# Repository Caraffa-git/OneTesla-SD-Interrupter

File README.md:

# OneTesla SD Interrupter 

re-created OneTesla SD Interrupter PCB based on files from [this page](https://onetesla.com/downloads)   

"original" version is PCB that tries to mimic the OneTesla PCB (with some small improvements), on the other hand "modified" version (for example) doesn't have useless battery holder footprints and has different layout

#### Note:
you have to install 1.1.4 version of SDFat lib for interrupter software, newer versions doesn't work

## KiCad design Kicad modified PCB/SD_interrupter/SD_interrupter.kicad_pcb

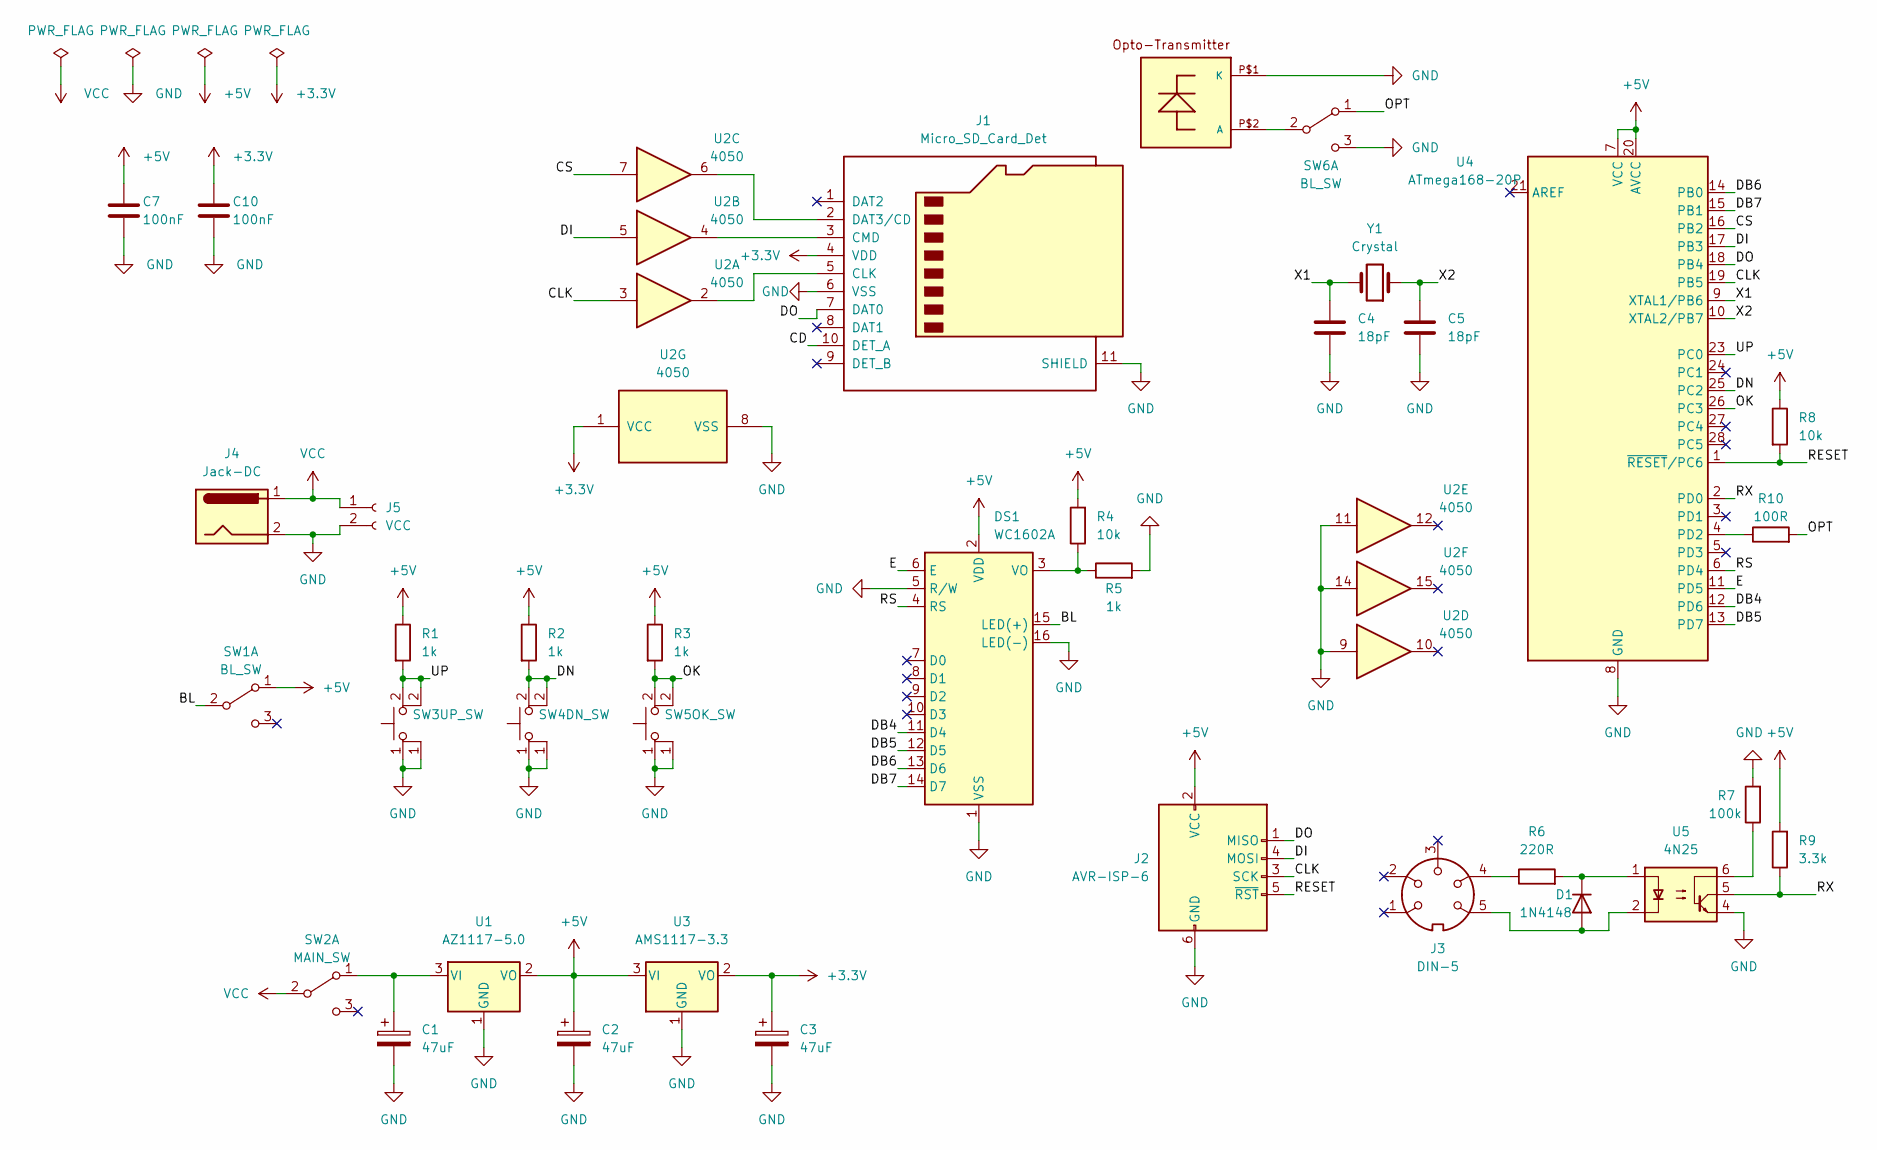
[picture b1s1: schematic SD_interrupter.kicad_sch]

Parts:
C1, C2, C3: 47uF; CP_Radial_D4.0mm_P1.50mm
C4, C5: 18pF; C_Disc_D5.1mm_W3.2mm_P5.00mm
C7, C10: 100nF; C_Disc_D5.1mm_W3.2mm_P5.00mm
D1: 1N4148; D_DO-35_SOD27_P7.62mm_Horizontal
DS1: WC1602A
J1: Micro_SD_Card_Det; microSD_HC_Hirose_DM3AT-SF-PEJM5
J2: AVR-ISP-6; PinSocket_2x03_P2.54mm_Vertical
J3: DIN-5; din-5
J4: Jack-DC; BarrelJack_Horizontal
J5: VCC; PinSocket_1x02_P2.54mm_Vertical
R1, R2, R3, R5: 1k; R_Axial_DIN0204_L3.6mm_D1.6mm_P7.62mm_Horizontal
R4, R8: 10k; R_Axial_DIN0204_L3.6mm_D1.6mm_P7.62mm_Horizontal
R6: 220R; R_Axial_DIN0204_L3.6mm_D1.6mm_P7.62mm_Horizontal
R7: 100k; R_Axial_DIN0204_L3.6mm_D1.6mm_P7.62mm_Horizontal
R9: 3.3k; R_Axial_DIN0204_L3.6mm_D1.6mm_P7.62mm_Horizontal
R10: 100R; R_Axial_DIN0204_L3.6mm_D1.6mm_P7.62mm_Horizontal
SW1, SW6: BL_SW; Switch 12x6mm
SW2: MAIN_SW; Switch 12x6mm
SW3: UP_SW; SW_PUSH_6mm_H7.3mm
SW4: DN_SW; SW_PUSH_6mm_H7.3mm
SW5: OK_SW; SW_PUSH_6mm_H7.3mm
U1: AZ1117-5.0; SOT-223-3_TabPin2
U2: 4050; DIP-16_W7.62mm
U3: AMS1117-3.3; SOT-223-3_TabPin2
U4: ATmega168-20P; DIP-28_W7.62mm
U5: 4N25; DIP-6_W7.62mm
U6: IFE91A; OPTO-TRANSMITTER
Y1: Crystal; Crystal_HC49-4H_Vertical

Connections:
+3.3V: C3.1, C10.1, J1.4 (VDD), U2.1 (VCC), U3.2 (VO)
+5V: C2.1, C7.1, DS1.2 (VDD), J2.2 (VCC), R1.1, R2.1, R3.1, R4.2, R8.1, R9.2, SW1.1 (A), U1.2 (VO), U3.3 (VI), U4.7 (VCC), U4.20 (AVCC)
/BL: DS1.15 (LED(+)), SW1.2 (B)
/CD: J1.10 (DET_A)
/CLK: J2.3 (SCK), U2.3, U4.19 (PB5)
/CS: U2.7, U4.16 (PB2)
/DB4: DS1.11 (D4), U4.12 (PD6)
/DB5: DS1.12 (D5), U4.13 (PD7)
/DB6: DS1.13 (D6), U4.14 (PB0)
/DB7: DS1.14 (D7), U4.15 (PB1)
/DI: J2.4 (MOSI), U2.5, U4.17 (PB3)
/DN: R2.2, SW4.2 (K), U4.25 (PC2)
/DO: J1.7 (DAT0), J2.1 (MISO), U4.18 (PB4)
/E: DS1.6 (E), U4.11 (PD5)
/OK: R3.2, SW5.2 (K), U4.26 (PC3)
/OPT: R10.2, SW6.1 (A)
/RESET: J2.5 (~RST), R8.2, U4.1 (~RESET/PC6)
/RS: DS1.4 (RS), U4.6 (PD4)
/RX: R9.1, U4.2 (PD0), U5.5
/UP: R1.2, SW3.2 (K), U4.23 (PC0)
/X1: C4.1, U4.9 (XTAL1/PB6), Y1.2
/X2: C5.1, U4.10 (XTAL2/PB7), Y1.1
GND: C1.2, C2.2, C3.2, C4.2, C5.2, C7.2, C10.2, DS1.1 (VSS), DS1.5 (R/W), DS1.16 (LED(-)), J1.6 (VSS), J1.11 (SHIELD), J2.6 (GND), J4.2, J5.2, R5.2, R7.2, SW3.1 (2), SW4.1, SW5.1 (2), SW6.3 (C), U1.1 (GND), U2.8 (VSS), U2.9, U2.11, U2.14, U3.1 (GND), U4.8 (GND), U4.22 (GND), U5.4, U6.P$1 (K)
unnamed: C1.1, SW2.1 (A), U1.3 (VI)
unnamed: D1.1 (K), R6.2, U5.1
unnamed: D1.2 (A), J3.5, U5.2
unnamed: DS1.3 (VO), R4.1, R5.1
unnamed: J1.2 (DAT3/CD), U2.6
unnamed: J1.3 (CMD), U2.4
unnamed: J1.5 (CLK), U2.2
unnamed: J3.4, R6.1
unnamed: R7.1, U5.6
unnamed: R10.1, U4.4 (PD2)
unnamed: SW6.2 (B), U6.P$2 (A)
VCC: J4.1, J5.1, SW2.2 (B)

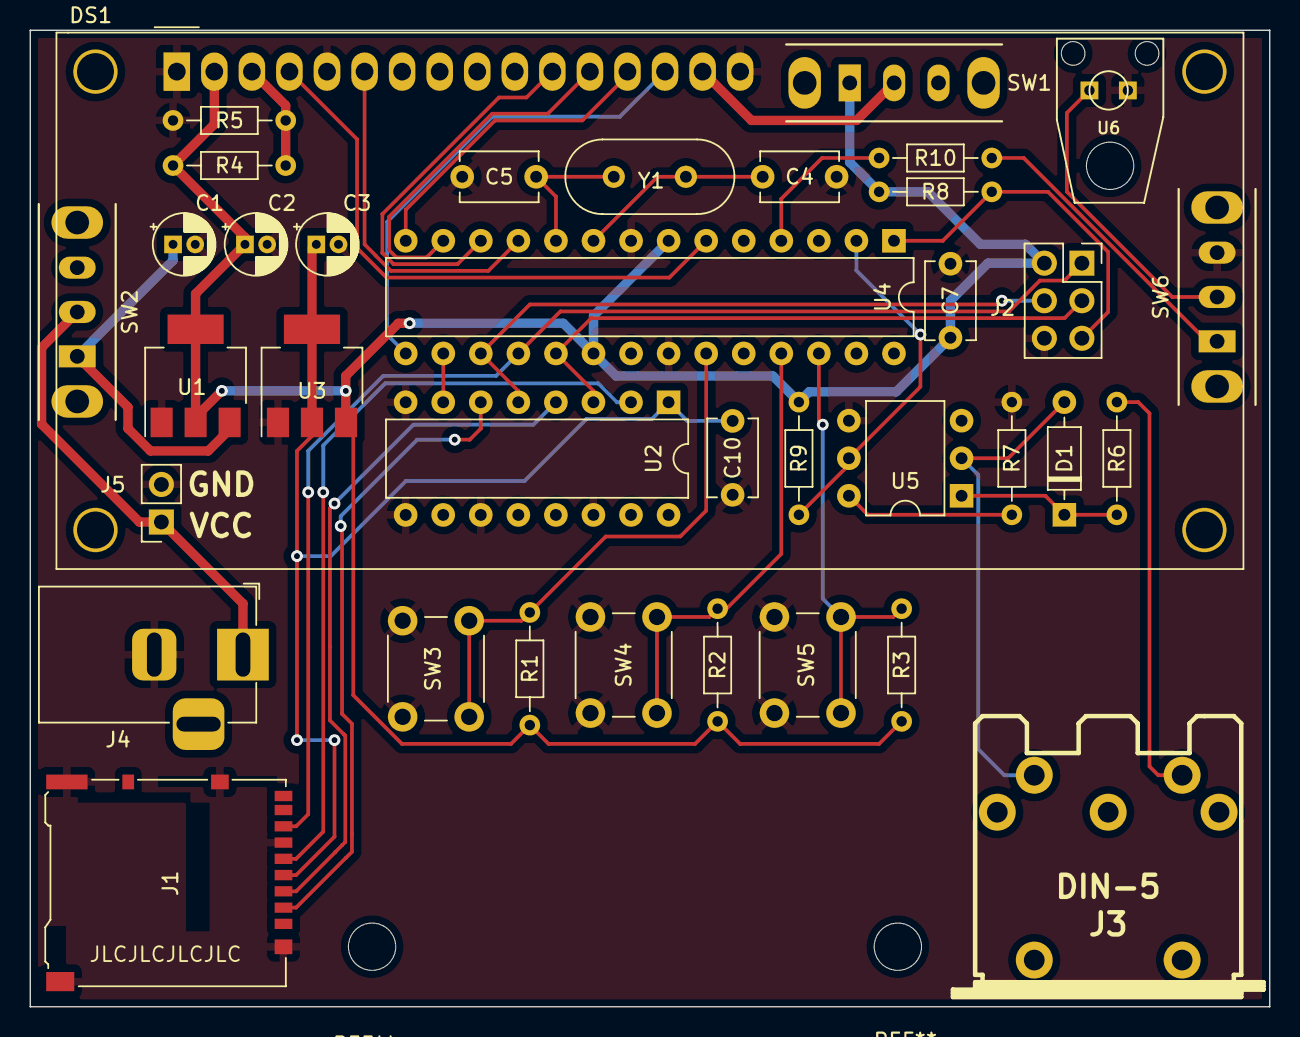
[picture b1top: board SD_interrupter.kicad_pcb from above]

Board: 2 copper layers, 83.8 x 66.0 mm, 37 parts (0 on the bottom side), 34 nets.

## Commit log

2022-07-10 Source files from OneTesla website
2022-07-10 PCB first commit
2022-07-11 nothing important
2022-07-11 Better PCB routing
2022-07-11 Minor changes
2022-08-02 different 3.3V regulator footprint
2022-08-03 gerbers update
2022-08-05 safety switch
2022-08-13 reorganization
2022-08-13 5V regulator footprint change
2022-08-13 gerbers
2022-08-28 github is broken
2022-09-12 updated software
